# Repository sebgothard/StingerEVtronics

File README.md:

# Manchester Stinger Motorsports Electronics
Hardware projects for Formula Student UK competition 2026-27.

💻Github https://github.com/sebgothard/StingerEVtronics

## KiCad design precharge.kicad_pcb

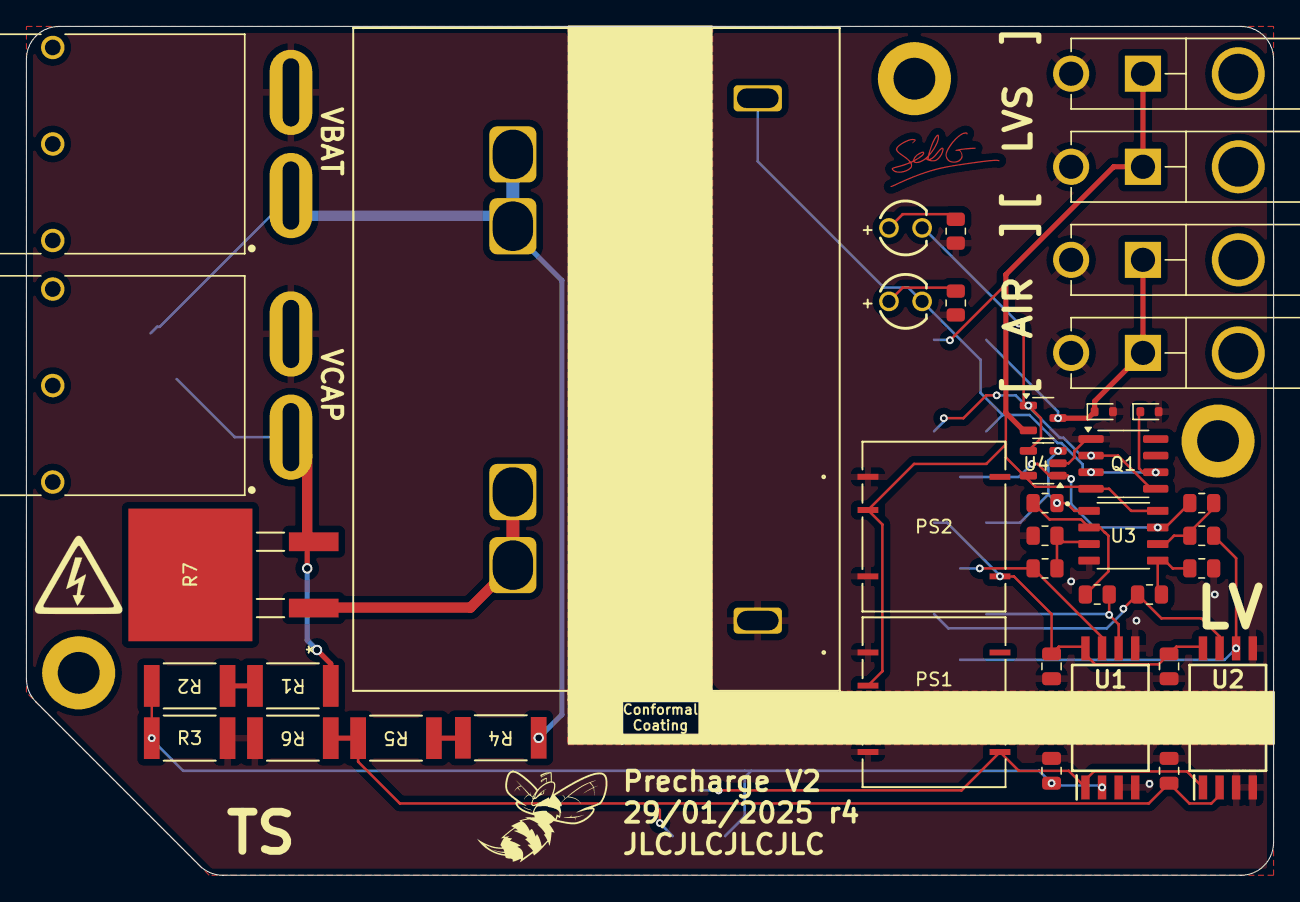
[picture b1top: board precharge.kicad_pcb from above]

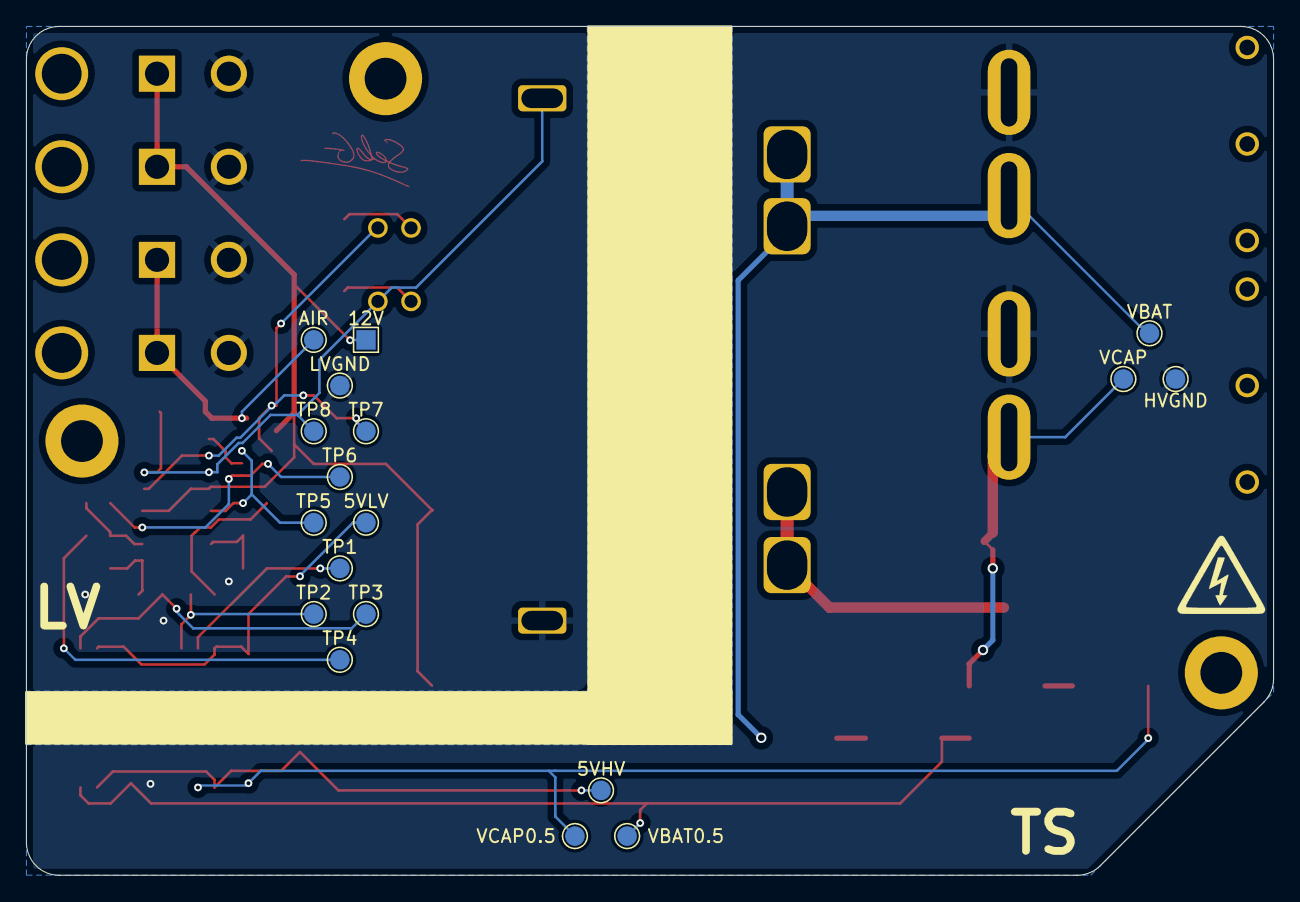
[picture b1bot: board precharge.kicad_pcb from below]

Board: 2 copper layers, 95.5 x 65.0 mm, 58 parts (18 on the bottom side), 27 nets.

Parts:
5VHV, 5VLV: TestPoint; TestPoint_Pad_D1.5mm
12V: TestPoint; TestPoint_Pad_1.5x1.5mm
AIR: TestPoint; TestPoint_Pad_D1.5mm
C3, C4, C5, C6: 100nF; C_0805_2012Metric
D1, D4: 1N4448X-TP; D_SOD-523
D2: 151031VS06000; WL-TMRC_3MM
D3: 151031SS06000; WL-TMRC_3MM
HVGND: TestPoint; TestPoint_Pad_D1.5mm
J1: CONN_AIR; MFJ_2X1
J2: TSAL_CONN_AIR; MFJ_2X1
J3: TSAL_CONN_LV; MFJ_2X1
J4: CONN_LV; MFJ_2X1
J5: CONN_HV; APP_ASMPR45-1X2-RK
J6: CONN_CAP; APP_ASMPR45-1X2-RK
K1: 12V; RELAY_G9KB-1A_OMR
LVGND: TestPoint; TestPoint_Pad_D1.5mm
PS1, PS2: PESE1-S12-S5-M-TR; SMD5_12.75X10.7X6.7_SINGLE_RCP
Q1: SI1539CDL-T1-GE3; SOIC-8_3.9x4.9mm_P1.27mm
Q2: NTR4003NT1G; SOT-23-3
R1, R4: 124K; RC2512N_VIS
R2, R5: 110K; RC2512N_VIS
R3, R6: 1K; RC2512N_VIS
R7: 15K; PWR263S-35-1002F_BRN
R8: 9K7; R_0805_2012Metric
R9, R10, R11, R12, R13, R14, R15: 10K; R_0805_2012Metric
R16, R17: 600; R_0805_2012Metric
TP1, TP2, TP3, TP4, TP5, TP6, TP7, TP8: TestPoint; TestPoint_Pad_D1.5mm
U1, U2: ACPL-C87A-500E; SOIC127P1150X361-8N
U3: MC33072DR2G; SOIC127P600X175-8N
U4: TL331; SOT-23-5
VBAT, VBAT0.5: TestPoint; TestPoint_Pad_D1.5mm
VCAP, VCAP0.5: TestPoint; TestPoint_Pad_D1.5mm

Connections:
+5V_HV: 5VHV.1, PS1.5 (+Vout), U1.1 (VDD1), U2.1 (VDD1)
+5V_LV: 5VLV.1, C3.2, C4.2, PS2.5 (+Vout), U1.8 (VDD2), U2.8 (VDD2)
+12V: 12V.1, J3.1, J4.1, PS1.2 (+Vin), PS2.2 (+Vin), Q1.4 (1), Q2.2 (D), U3.8 (V+), U4.5 (V+)
AIR-COIL: AIR.1, D4.1 (K), J1.1, J2.1, Q2.3 (S)
AIR-FET: D2.2 (A), Q1.2 (G), Q1.5 (G), Q2.1 (G), TP7.1, U4.4
CHARGE-COIL: D1.1 (K), D3.2 (A), K1.2, Q1.3 (D), Q1.6 (D), TP8.1
HVGND: C5.2, C6.2, HVGND.1, J5.2, J6.2, PS1.4 (-Vout), R3.2, R6.2, U1.3 (IN-), U1.4 (GND1), U2.3 (IN-), U2.4 (GND1)
LVGND: C3.1, C4.1, D1.2 (A), D4.2 (A), J1.2, J2.2, J3.2, J4.2, K1.1, LVGND.1, PS1.1 (-Vin), PS2.1 (-Vin), PS2.4 (-Vout), Q1.1 (S), R11.1, R15.1, R16.2, R17.2, U1.5 (GND2), U2.5 (GND2), U3.4 (V-), U4.2 (V-)
unnamed: D2.1 (K), R16.1
unnamed: D3.1 (K), R17.1
unnamed: K1.3, K1.5, R7.1
unnamed: R1.2, R2.1
unnamed: R4.2, R5.1
unnamed: R9.1, TP1.1, U1.7 (OUT+)
unnamed: R10.1, TP2.1, U1.6 (OUT-)
unnamed: R13.1, TP3.1, U2.7 (OUT+)
unnamed: R14.1, TP4.1, U2.6 (OUT-)
unnamed: R9.2, R11.2, U3.3 (+)
unnamed: R10.2, R12.1, U3.2 (-)
unnamed: R13.2, R15.2, U3.5 (+)
unnamed: R8.1, R14.2, U3.6 (-)
unnamed: R12.2, TP5.1, U3.1, U4.3 (+)
unnamed: R8.2, TP6.1, U3.7, U4.1 (-)
VBAT: J5.1, K1.4, K1.6, R4.1, VBAT.1
VBAT-0.5%: C6.1, R5.2, R6.1, U2.2 (IN), VBAT0.5.1
VCAP: J6.1, R1.1, R7.2, VCAP.1
VCAP-0.5%: C5.1, R2.2, R3.1, U1.2 (IN), VCAP0.5.1

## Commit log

2025-01-30 Pushing precharge.
